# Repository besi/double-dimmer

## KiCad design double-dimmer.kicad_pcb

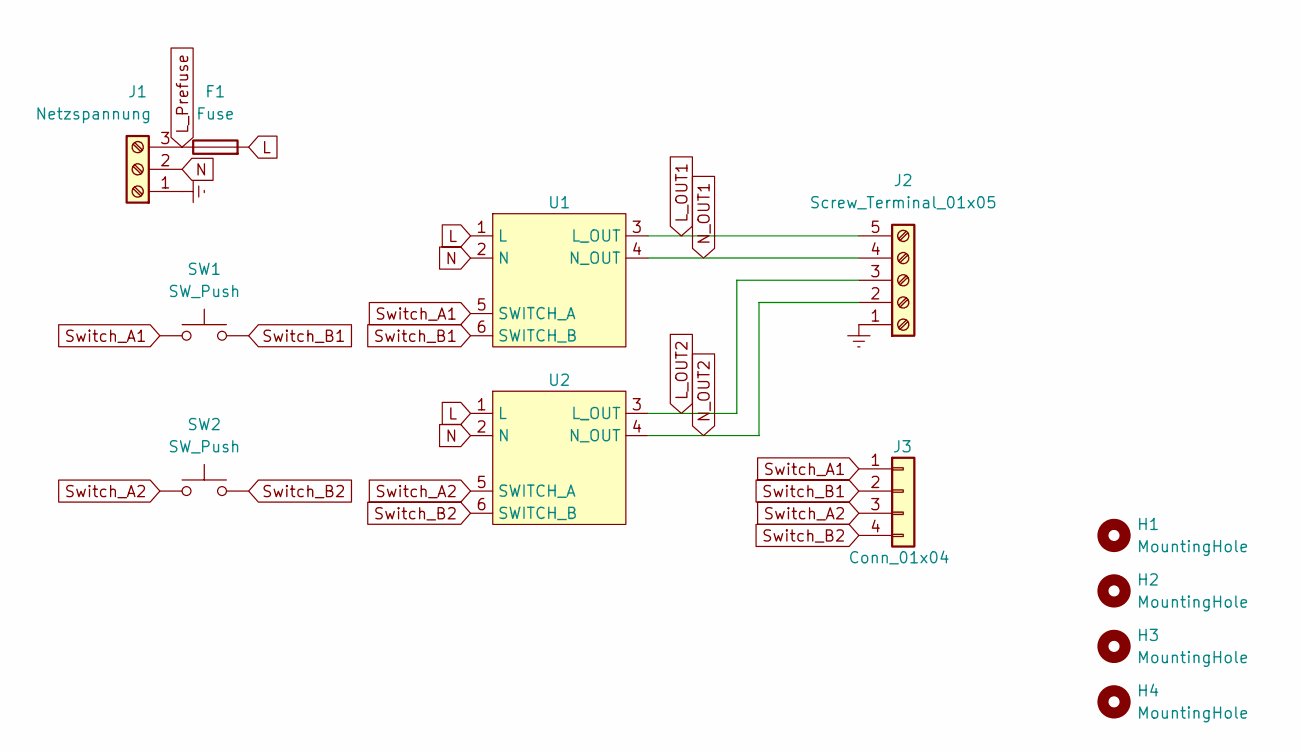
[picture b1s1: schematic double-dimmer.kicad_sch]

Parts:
F1: Fuse; Fuseholder_Cylinder-5x20mm_Schurter_0031_8201_Horizontal_Op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
H1, H2, H3, H4: MountingHole; MountingHole_3.2mm_M3
J1: Netzspannung; TerminalBlock_Phoenix_MKDS-1,5-3-5.08_1x03_P5.08mm_Horizont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
J2: Screw_Terminal_01x05; TerminalBlock_Phoenix_MKDS-1,5-5-5.08_1x05_P5.08mm_Horizont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
J3: Conn_01x04; PinHeader_1x04_P2.54mm_Vertical
SW1, SW2: SW_Push; pts636
U1, U2: dimmer

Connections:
Earth: J1.1, J2.1
L: F1.2, U1.1 (L), U2.1 (L)
L_OUT1: J2.5, U1.3 (L_OUT)
L_OUT2: J2.3, U2.3 (L_OUT)
L_Prefuse: F1.1, J1.3
N: J1.2, U1.2 (N), U2.2 (N)
N_OUT1: J2.4, U1.4 (N_OUT)
N_OUT2: J2.2, U2.4 (N_OUT)
Switch_A1: J3.1, SW1.2, U1.5 (SWITCH_A)
Switch_A2: J3.3, SW2.2, U2.5 (SWITCH_A)
Switch_B1: J3.2, SW1.1, U1.6 (SWITCH_B)
Switch_B2: J3.4, SW2.1, U2.6 (SWITCH_B)

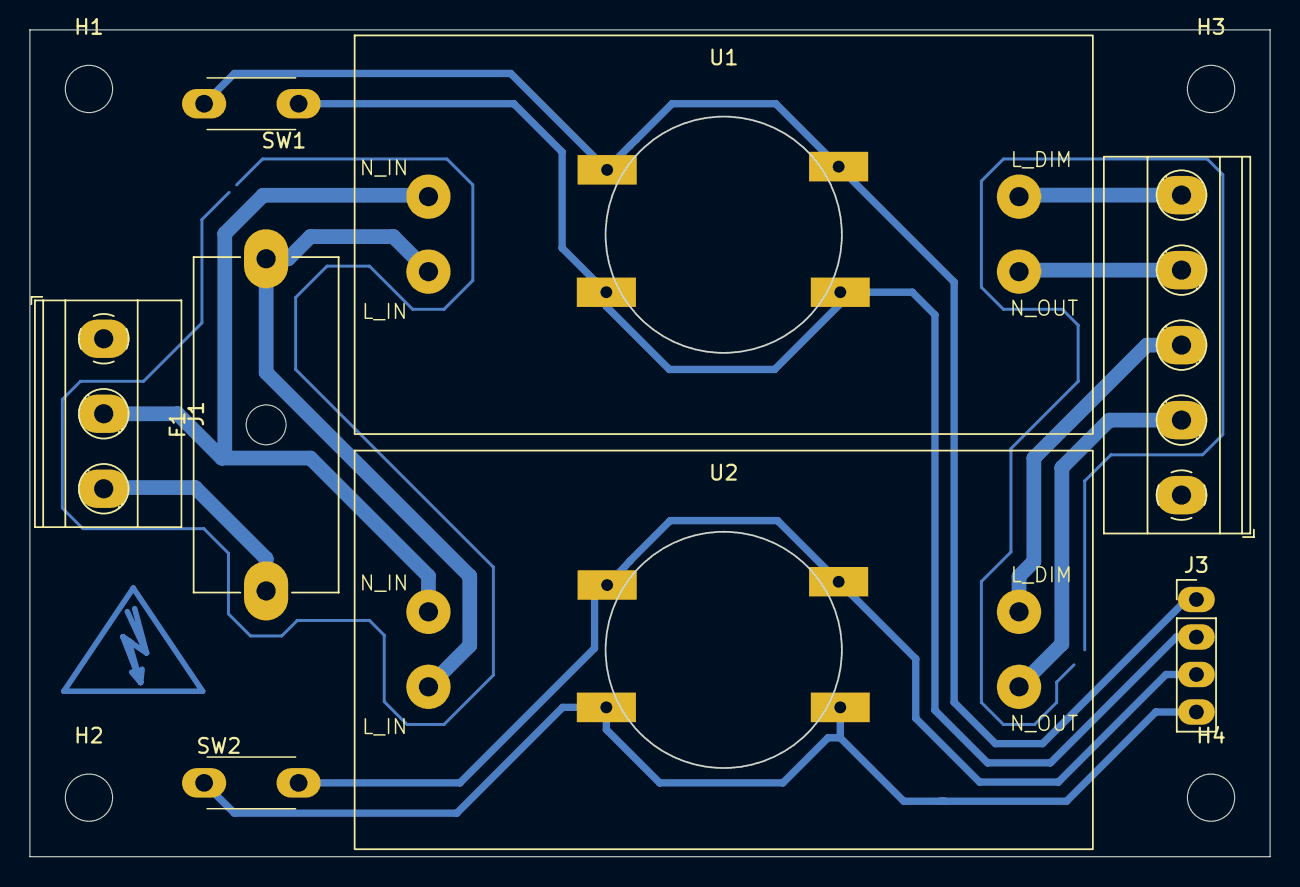
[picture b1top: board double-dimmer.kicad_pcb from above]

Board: 2 copper layers, 83.9 x 55.9 mm, 12 parts (0 on the bottom side), 12 nets.

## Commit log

2024-09-04 Initial Dobule dimmer schematic
2024-09-04 Add screenshot and update missing schematic
2024-09-05 Update dimmer footprint and add fuse and a switch
2024-09-05 Update dimmer footprint and symbol
2024-09-06 Added switches to layout and do routing
2024-09-06 Properly label the dimmers terminals
2024-09-06 Add mounting holes
2024-09-06 Add warning sign
2024-09-06 Add drill place origin
2024-09-06 Plotting the PCB + step file
2024-09-06 Step file location
2024-09-06 Add cncGraf screenshot
